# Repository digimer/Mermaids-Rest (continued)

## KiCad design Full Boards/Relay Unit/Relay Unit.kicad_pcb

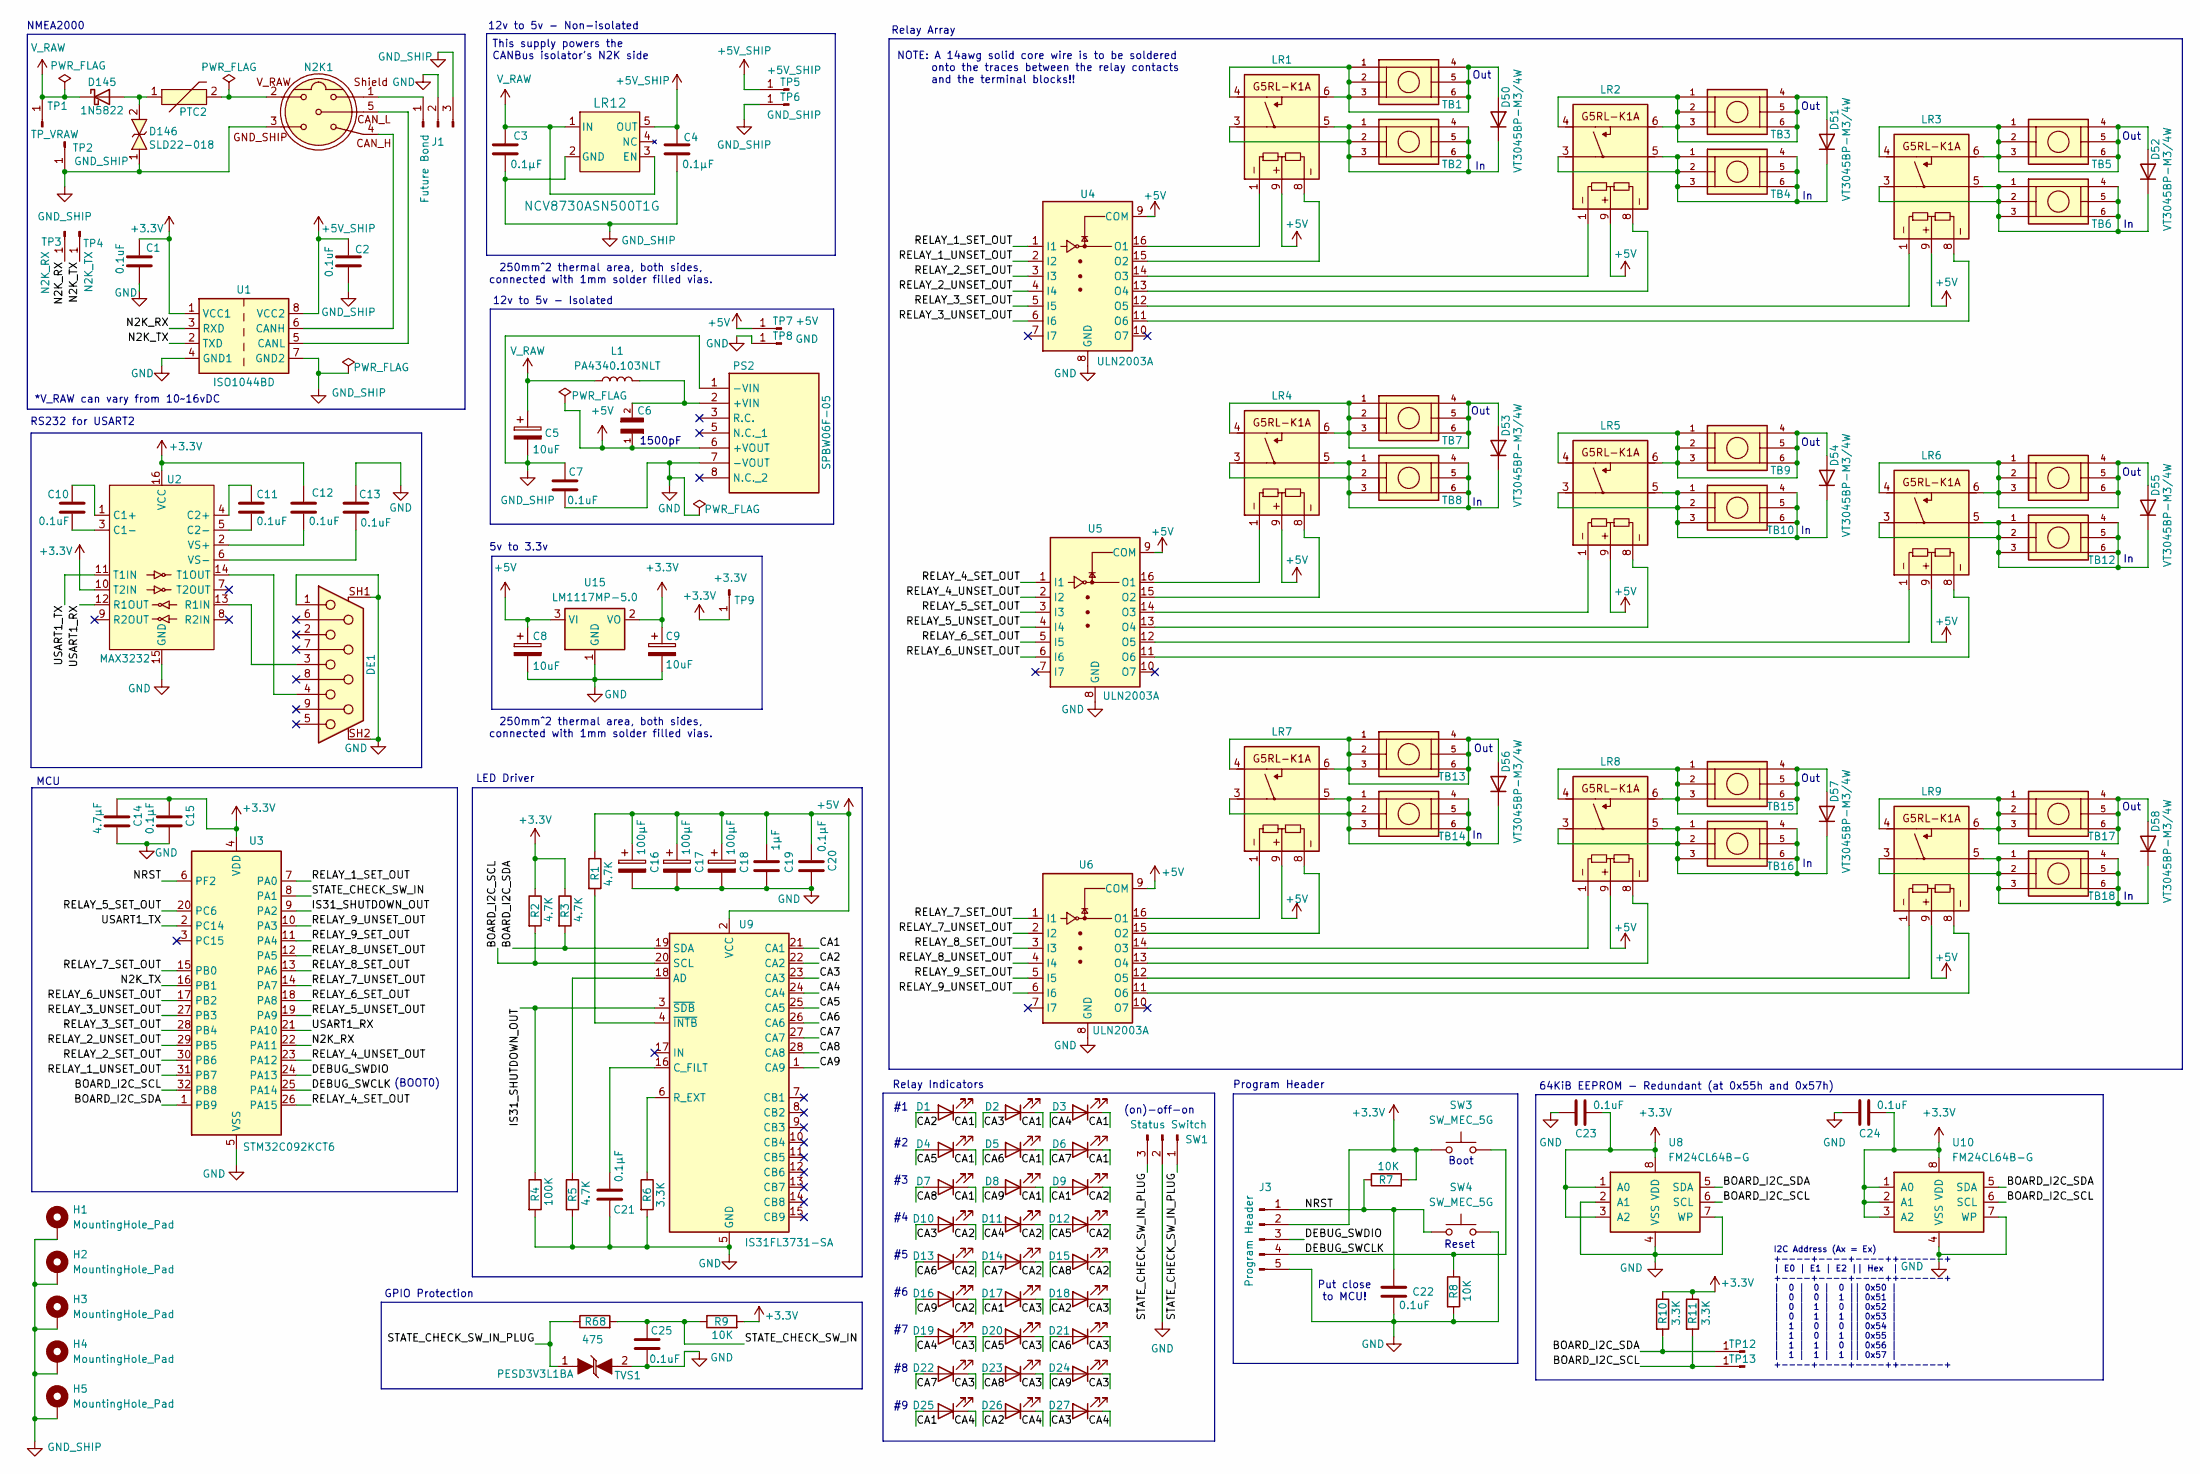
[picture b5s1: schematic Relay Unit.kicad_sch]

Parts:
C1, C2, C7, C10, C11, C12, C13, C22, C23, C24, C25: 0.1uF; RCE5C1H104J2A2H03B
C3, C4, C15, C20, C21: 0.1μF; RCE5C1H104J2A2H03B
C5, C8, C9: 10uF; CP_Radial_D8.0mm_P3.50mm
C6: TDK FA28NP01H152JNU06; TDK CAPRB500W50L400T250H550; PARTREV 20200318
C14: 4.7μF; RCER71E475K2A2H03B
C16, C17, C18: 100μF; CP_Radial_D8.0mm_P5.00mm
C19: 1μF; C_Rect_L7.2mm_W7.2mm_P5.00mm_FKS2_FKP2_MKS2_MKP2
D1, D2, D3, D4, D5, D6, D7, D8, D9, D10, D11, D12, D13, D14, D15, D16, D17, D18, D19, D20, D21, D22, D23, D24, D25, D26, D27: LED; WP383SURDTK
D50, D51, D52, D53, D54, D55, D56, D57, D58: VT3045BP-M3/4W; Vishay VT3045BP-M3_4W_VIS
D145: 1N5822; D_DO-201AD_P15.24mm_Horizontal
D146: SLD22-018; DIOAD4425W136L885D885; Manufacturer_Part_Number SLD15-018; Mouser Part Number 576-SLD15-018
DE1: Amphenol_L77SDE09SA4CH4F
H1, H2, H3, H4, H5: MountingHole_Pad; MountingHole_4mm_Pad_Via
J1: Future Bond; PinHeader_1x03_P2.54mm_Vertical
J3: Program Header; PinHeader_1x05_P2.54mm_Horizontal
L1: PA4340.103NLT; Pulse PA4340.103NLT
LR1, LR2, LR3, LR4, LR5, LR6, LR7, LR8, LR9: G5RL-K1A
LR12: NCV8730ASN500T1G; TSOP-5_483_OSI
N2K1: M12B-05PMMR
PS2: SPBW06F-05; SPBW06F05; Manufacturer_Part_Number SPBW06F-05; Mouser Part Number 709-SPBW06F-05
PTC2: PTC; AHEF100
R1, R2, R3, R5: 4.7K; R_Axial_DIN0207_L6.3mm_D2.5mm_P7.62mm_Horizontal
R4: 100K; R_Axial_DIN0207_L6.3mm_D2.5mm_P7.62mm_Horizontal
R6, R10, R11: 3.3K; R_Axial_DIN0207_L6.3mm_D2.5mm_P7.62mm_Horizontal
R7, R8, R9: 10K; R_Axial_DIN0207_L6.3mm_D2.5mm_P7.62mm_Horizontal
R68: 475; R_Axial_DIN0207_L6.3mm_D2.5mm_P7.62mm_Horizontal
SW1: Status Switch; PinHeader_1x03_P2.54mm_Horizontal
SW3, SW4: SW_MEC_5G; SW_TS03-66-50-BK-160-LCR-D-67
TB1, TB2, TB3, TB4, TB5, TB6, TB7, TB8, TB9, TB10, TB11, TB12, TB13, TB14, TB15, TB16, TB17, TB18: Keystone Electronics 7799; Keystone 7799; PARTREV C
TP1: TP_VRAW; PinHeader_1x01_P2.54mm_Vertical
TP2, TP6, TP13: GND_SHIP; PinHeader_1x01_P2.54mm_Vertical
TP3: N2K_RX; PinHeader_1x01_P2.54mm_Vertical
TP4: N2K_TX; PinHeader_1x01_P2.54mm_Vertical
TP5, TP12: +5V_SHIP; PinHeader_1x01_P2.54mm_Vertical
TP7: +5V; PinHeader_1x01_P2.54mm_Vertical
TP8: GND; PinHeader_1x01_P2.54mm_Vertical
TP9: +3.3V; PinHeader_1x01_P2.54mm_Vertical
TVS1: PESD3V3L1BA; D_SOD-323
U1: ISO1044BD; SOIC-8_3.9x4.9mm_P1.27mm
U2: MAX3232; TSSOP-16_4.4x5mm_P0.65mm
U3: STM32C092KCT6; QFN-32-1EP_5x5mm_P0.5mm_EP3.45x3.45mm
U4, U5, U6: ULN2003A; DIP-16_W7.62mm
U8, U10: FM24CL64B-G; SOIC-8_3.9x4.9mm_P1.27mm
U9: IS31FL3731-SA; SSOP-28_5.3x10.2mm_P0.65mm
U15: LM1117MP-5.0; SOT-223-3_TabPin2

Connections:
+3.3V: C1.1, C9.1, C12.1, C14.1, C15.1, C23.1, C24.1, J3.2, R2.1, R3.1, R7.2, R9.2, R10.1, R11.1, SW3.1 (A), SW3.2 (A), TP9.1, U1.1 (VCC1), U2.10 (T2IN), U2.16 (VCC), U3.4 (VDD), U8.1 (A0), U8.3 (A2), U8.8 (VDD), U10.1 (A0), U10.2 (A1), U10.3 (A2), U10.8 (VDD), U15.2 (VO)
+5V: C6.1, C8.1, C16.1, C17.1, C18.1, C19.1, C20.1, LR1.9, LR2.9, LR3.9, LR4.9, LR5.9, LR6.9, LR7.9, LR8.9, LR9.9, PS2.6 (+VOUT), R1.1, TP7.1, U4.9 (COM), U5.9 (COM), U6.9 (COM), U9.2 (VCC), U15.3 (VI)
+5V_SHIP: C2.1, C4.1, LR12.5 (OUT), TP5.1, U1.8 (VCC2)
/BOARD_I2C_SCL: R2.2, R11.2, TP13.1, U3.32 (PB8), U8.6 (SCL), U9.20 (SCL), U10.6 (SCL)
/BOARD_I2C_SDA: R3.2, R10.2, TP12.1, U3.1 (PB9), U8.5 (SDA), U9.19 (SDA), U10.5 (SDA)
/CA1: D1.1 (K), D2.1 (K), D3.1 (K), D4.1 (K), D5.1 (K), D6.1 (K), D7.1 (K), D8.1 (K), D9.2 (A), D17.2 (A), D25.2 (A), U9.21 (CA1)
/CA2: D1.2 (A), D9.1 (K), D10.1 (K), D11.1 (K), D12.1 (K), D13.1 (K), D14.1 (K), D15.1 (K), D16.1 (K), D18.2 (A), D26.2 (A), U9.22 (CA2)
/CA3: D2.2 (A), D10.2 (A), D17.1 (K), D18.1 (K), D19.1 (K), D20.1 (K), D21.1 (K), D22.1 (K), D23.1 (K), D24.1 (K), D27.2 (A), U9.23 (CA3)
/CA4: D3.2 (A), D11.2 (A), D19.2 (A), D25.1 (K), D26.1 (K), D27.1 (K), U9.24 (CA4)
/CA5: D4.2 (A), D12.2 (A), D20.2 (A), U9.25 (CA5)
/CA6: D5.2 (A), D13.2 (A), D21.2 (A), U9.26 (CA6)
/CA7: D6.2 (A), D14.2 (A), D22.2 (A), U9.27 (CA7)
/CA8: D7.2 (A), D15.2 (A), D23.2 (A), U9.28 (CA8)
/CA9: D8.2 (A), D16.2 (A), D24.2 (A), U9.1 (CA9)
/DEBUG_SWCLK: J3.4, R8.1, SW3.3 (B), SW3.4 (B), U3.25 (PA14)
/DEBUG_SWDIO: J3.3, U3.24 (PA13)
/IS31_SHUTDOWN_OUT: R4.1, U3.9 (PA2), U9.3 (~SDB)
/N2K_RX: TP3.1, U1.3 (RXD), U3.22 (PA11)
/N2K_TX: TP4.1, U1.2 (TXD), U3.16 (PB1)
/NRST: C22.1, J3.1, R7.1, SW4.1 (A), SW4.2 (A), U3.6 (PF2)
/RELAY_1_SET_OUT: U3.7 (PA0), U4.1 (I1)
/RELAY_1_UNSET_OUT: U3.31 (PB7), U4.2 (I2)
/RELAY_2_SET_OUT: U3.30 (PB6), U4.3 (I3)
/RELAY_2_UNSET_OUT: U3.29 (PB5), U4.4 (I4)
/RELAY_3_SET_OUT: U3.28 (PB4), U4.5 (I5)
/RELAY_3_UNSET_OUT: U3.27 (PB3), U4.6 (I6)
/RELAY_4_SET_OUT: U3.26 (PA15), U5.1 (I1)
/RELAY_4_UNSET_OUT: U3.23 (PA12), U5.2 (I2)
/RELAY_5_SET_OUT: U3.20 (PC6), U5.3 (I3)
/RELAY_5_UNSET_OUT: U3.19 (PA9), U5.4 (I4)
/RELAY_6_SET_OUT: U3.18 (PA8), U5.5 (I5)
/RELAY_6_UNSET_OUT: U3.17 (PB2), U5.6 (I6)
/RELAY_7_SET_OUT: U3.15 (PB0), U6.1 (I1)
/RELAY_7_UNSET_OUT: U3.14 (PA7), U6.2 (I2)
/RELAY_8_SET_OUT: U3.13 (PA6), U6.3 (I3)
/RELAY_8_UNSET_OUT: U3.12 (PA5), U6.4 (I4)
/RELAY_9_SET_OUT: U3.11 (PA4), U6.5 (I5)
/RELAY_9_UNSET_OUT: U3.10 (PA3), U6.6 (I6)
/STATE_CHECK_SW_IN: C25.1, R9.1, R68.2, U3.8 (PA1)
/STATE_CHECK_SW_IN_PLUG: R68.1, SW1.1, SW1.3, TVS1.1
/USART1_RX: U2.12 (R1OUT), U3.21 (PA10)
/USART1_TX: U2.11 (T1IN), U3.2 (PC14)
GND: C1.2, C7.2, C8.2, C9.2, C13.2, C14.2, C15.2, C16.2, C17.2, C18.2, C19.2, C20.2, C21.2, C22.2, C23.2, C24.2, C25.2, DE1.1, DE1.SH1, DE1.SH2, J1.2, J3.5, PS2.7 (-VOUT), R4.2, R5.2, R6.2, R8.2, SW1.2, SW4.3 (B), SW4.4 (B), TP8.1, TVS1.2, U1.4 (GND1), U2.15 (GND), U3.5 (VSS), U3.33 (VSS), U4.8 (GND), U5.8 (GND), U6.8 (GND), U8.2 (A1), U8.4 (VSS), U8.7 (WP), U9.5 (GND), U10.4 (VSS), U10.7 (WP), U15.1 (GND)
GND_SHIP: C2.2, C3.2, C4.2, C5.2, C7.1, D146.1, H1.1, H2.1, H3.1, H4.1, H5.1, J1.3, LR12.2 (GND), N2K1.3, PS2.1 (-VIN), TP2.1, TP6.1, U1.7 (GND2)
unnamed: D50.2 (A), LR1.4, LR1.6, TB1.1, TB1.2, TB1.3, TB1.4, TB1.5, TB1.6
unnamed: D50.1 (K), LR1.3, LR1.5, TB2.1, TB2.2, TB2.3, TB2.4, TB2.5, TB2.6
unnamed: D51.2 (A), LR2.4, LR2.6, TB3.1, TB3.2, TB3.3, TB3.4, TB3.5, TB3.6
unnamed: D51.1 (K), LR2.3, LR2.5, TB4.1, TB4.2, TB4.3, TB4.4, TB4.5, TB4.6
unnamed: D52.2 (A), LR3.4, LR3.6, TB5.1, TB5.2, TB5.3, TB5.4, TB5.5, TB5.6
unnamed: D52.1 (K), LR3.3, LR3.5, TB6.1, TB6.2, TB6.3, TB6.4, TB6.5, TB6.6
unnamed: D53.2 (A), LR4.4, LR4.6, TB7.1, TB7.2, TB7.3, TB7.4, TB7.5, TB7.6
unnamed: D53.1 (K), LR4.3, LR4.5, TB8.1, TB8.2, TB8.3, TB8.4, TB8.5, TB8.6
unnamed: D54.2 (A), LR5.4, LR5.6, TB9.1, TB9.2, TB9.3, TB9.4, TB9.5, TB9.6
unnamed: D54.1 (K), LR5.3, LR5.5, TB10.1, TB10.2, TB10.3, TB10.4, TB10.5, TB10.6
unnamed: D55.2 (A), LR6.4, LR6.6, TB11.1, TB11.2, TB11.3, TB11.4, TB11.5, TB11.6
unnamed: D55.1 (K), LR6.3, LR6.5, TB12.1, TB12.2, TB12.3, TB12.4, TB12.5, TB12.6
unnamed: D56.2 (A), LR7.4, LR7.6, TB13.1, TB13.2, TB13.3, TB13.4, TB13.5, TB13.6
unnamed: D56.1 (K), LR7.3, LR7.5, TB14.1, TB14.2, TB14.3, TB14.4, TB14.5, TB14.6
unnamed: D57.2 (A), LR8.4, LR8.6, TB15.1, TB15.2, TB15.3, TB15.4, TB15.5, TB15.6
unnamed: D57.1 (K), LR8.3, LR8.5, TB16.1, TB16.2, TB16.3, TB16.4, TB16.5, TB16.6
unnamed: D58.2 (A), LR9.4, LR9.6, TB17.1, TB17.2, TB17.3, TB17.4, TB17.5, TB17.6
unnamed: D58.1 (K), LR9.3, LR9.5, TB18.1, TB18.2, TB18.3, TB18.4, TB18.5, TB18.6
unnamed: D145.2 (A), D146.2, PTC2.1
unnamed: J1.1, N2K1.1
unnamed: N2K1.2, PTC2.2
unnamed: C6.2, L1.2, PS2.2 (+VIN)
unnamed: N2K1.4, U1.6 (CANH)
unnamed: N2K1.5, U1.5 (CANL)
unnamed: C10.1, U2.1 (C1+)
unnamed: C10.2, U2.3 (C1-)
unnamed: C11.1, U2.4 (C2+)
unnamed: C11.2, U2.5 (C2-)
unnamed: DE1.3, U2.13 (R1IN)
unnamed: DE1.4, U2.14 (T1OUT)
unnamed: C12.2, U2.2 (VS+)
unnamed: C13.1, U2.6 (VS-)
unnamed: LR1.1, U4.16 (O1)
unnamed: LR1.8, U4.15 (O2)
unnamed: LR2.1, U4.14 (O3)
unnamed: LR2.8, U4.13 (O4)
unnamed: LR3.1, U4.12 (O5)
unnamed: LR3.8, U4.11 (O6)
unnamed: LR4.1, U5.16 (O1)
unnamed: LR4.8, U5.15 (O2)
unnamed: LR5.1, U5.14 (O3)
unnamed: LR5.8, U5.13 (O4)
unnamed: LR6.1, U5.12 (O5)
unnamed: LR6.8, U5.11 (O6)
unnamed: LR7.1, U6.16 (O1)
unnamed: LR7.8, U6.15 (O2)
unnamed: LR8.1, U6.14 (O3)
unnamed: LR8.8, U6.13 (O4)
unnamed: LR9.1, U6.12 (O5)
unnamed: LR9.8, U6.11 (O6)
unnamed: R5.1, U9.18 (AD)
unnamed: C21.1, U9.16 (C_FILT)
unnamed: R6.1, U9.6 (R_EXT)
unnamed: R1.2, U9.4 (~INTB)
V_RAW: C3.1, C5.1, D145.1 (K), L1.1, LR12.1 (IN), LR12.3 (EN), TP1.1

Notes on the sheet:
Reset
(on)-off-on
NOTE: A 14awg solid core wire is to be soldered onto the traces between the relay contacts and the terminal blocks!!
Boot
GPIO Protection
250mm^2 thermal area, both sides, connected with 1mm solder filled vias.
MCU
This supply powers the CANBus isolator's N2K side
64KiB EEPROM - Redundant (at 0x55h and 0x57h)
12v to 5v - Isolated
*V_RAW can vary from 10~16vDC
Out
Program Header
5v to 3.3v
(BOOT0)
12v to 5v - Non-isolated
Put close to MCU!
RS232 for USART2
LED Driver
Relay Indicators
NMEA2000
Relay Array
1500pF
I2C Address (Ax = Ex) +----+----+----++------+ | E0 | E1 | E2 || Hex | +----+----+----++------+ | 0 | 0 | 0 || 0x50 | | 0 | 0 | 1 || 0x51 | | 0 | 1 | 0 || 0x52 | | 0 | 1 | 1 || 0x53 | | 1 | 0 | 0 || 0x54 | | 1 | 0 | 1 || 0x55 | | 1 | 1 | 0 || 0x56 | | 1 | 1 | 1 || 0x57 | +----+----+----++------+

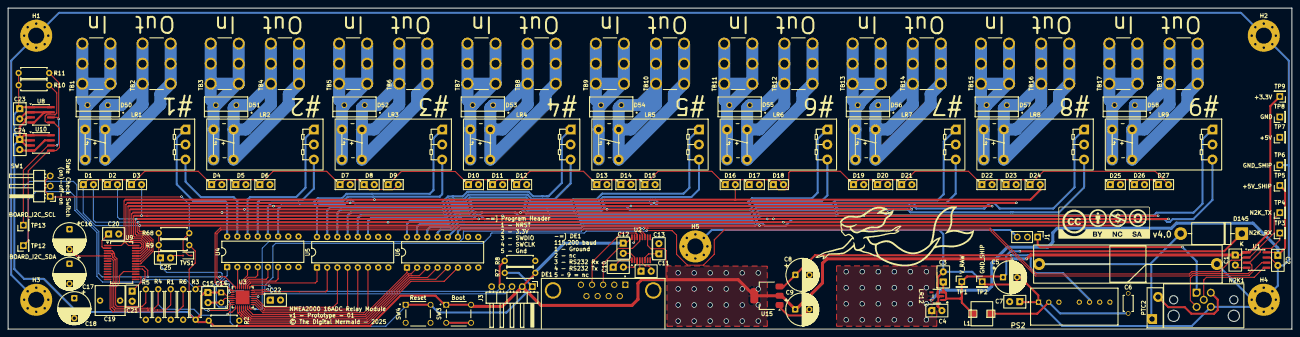
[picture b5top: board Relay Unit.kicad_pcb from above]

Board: 4 copper layers, 320.0 x 80.0 mm, 140 parts (0 on the bottom side), 99 nets.
